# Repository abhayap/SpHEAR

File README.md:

# The *SpHEAR Project

The *SpHEAR (Spherical Harmonics Ear) Project is a collection of 3D models and associated code for building, testing and calibrating full surround Ambisonics microphones. All 3D models are written in Openscad with the code licensed under the GPL 3+ license (GNU Public License version 3 or higher), and the 3D models licensed under the Creative Commons Attribution-NonCommercial-ShareAlike 4.0 International license.

The 3D models are almost completely parametric and are designed to be able to be printed on low cost widely available 3D printers (at CCRMA we use an Ultimaker 2 Extended Plus printer, using PLA material). The design is modular and tries to avoid using overhangs and support structures. That is why each microphone assembly is made of a number of independently printed capsule holders interconnected by legs that interlock and hold the structure together. The capsule holders and the mount are glued together to create a 3D structure that securely holds all microphone capsules. A mount that can be clipped into a standard microphone stand is part of the design.

## Mailing list

You can subscribe to a development mailing list (sphear-devel@ccrma.stanford.edu) here:
<https://cm-mail.stanford.edu/mailman/listinfo/sphear-devel>

## About building microphones

Successfully printing a microphone assembly is only the first step in a long and complicated process. This also includes finding and buying the required microphone capsules, assembling the electronics (requires precision skill with the soldering iron) and finally calibrating the multi-capsule microphone to get the best performance out of it (you will need at least a single driver sound source and a calibrated microphone).

The whole process is not easy and requires knowledge of acoustics and electronics, plus a healthy dose of patience and the ability to perform tasks with precision and care. This repository will eventually include more detailed instructions, electronic schematics, suggested and tested parts and software and procedures for calibrating and measuring the microphone, including models for test and calibration rigs.

## 3D models

The 3D models currently include the TinySpHEAR, a four capsule first order Ambisonics microphone, the Octathingy, an eight capsule second order design by Eric Benjamin and Aaron Heller and preliminary designs for 12 and 20 capsule designs (the BigSpHEAR_12 and BigSpHEAR_20 models). The models will be expanded as testing proceeds. 

* [TinySpHEAR](doc/TinySpHEAR_simple.md): four capsule first order microphone with simple stand mount

  * [TinySpHEAR Zapnspark](doc/TinySpHEAR_zapnspark.md): four capsule first order microphone with four Zapnspark phantom power interfaces and shock mount

* [Octathingy](): eight capsule microphone (proof of concept so far)

* [BigSpHEAR_12 / BigSpHEAR_20](): 12 and 20 capsule designs (proof of concept)

## Electronics

The pcb/zapnspark directory contains the Kicad electrical circuit and printed circuit board design for the Zapnspark phantom power interface. The current printed circuit board design fits into four slots carved inside the body of the [TinySpHEAR plus Zapnspark model](doc/TinySpHEAR_zapnspark.md). Everything is dimensioned for the sizes of the components specified in the parts list, any changes (specially the diameter of the electrolytic capacitors) would need to be taken into account by changing appropriate model parameters. 

## Calibration

The calibration/src directory contains the Octave files for the current calibration software. The CALIBRATION.md file in there has a very brief description of usage, but currently is out of date with the current source code. Look into the individual files for more guidance. Hopefully this will be fixed soon.

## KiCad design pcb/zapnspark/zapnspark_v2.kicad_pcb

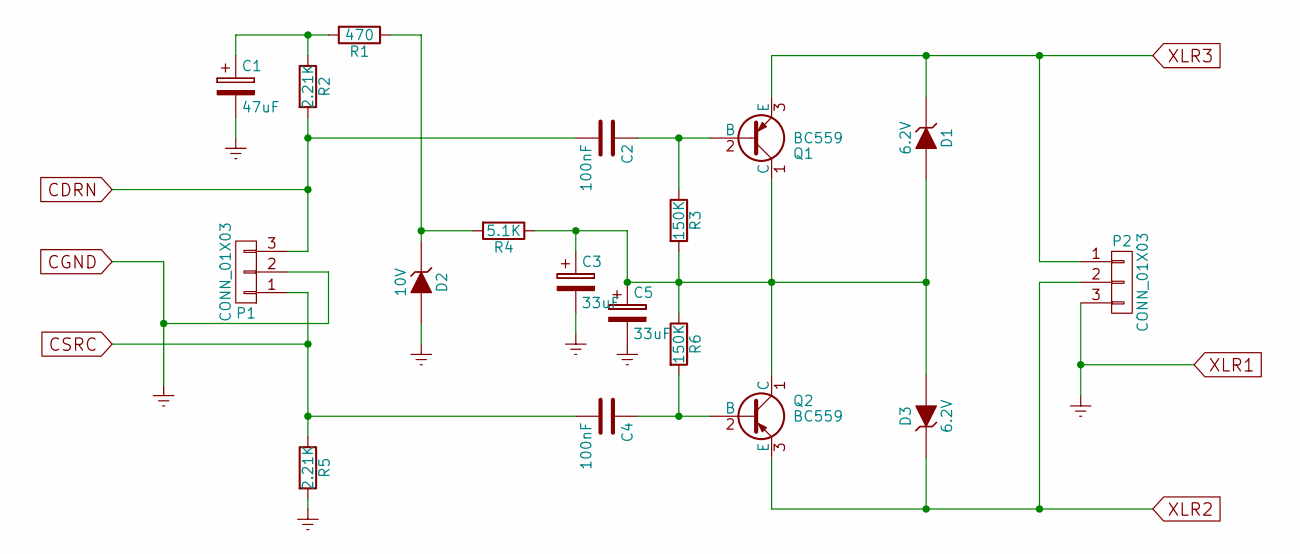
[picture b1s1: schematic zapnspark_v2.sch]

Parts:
C1: 47uF; C_Radial_D8_L13_P3.8
C2, C4: 100nF; C_Rect_L13_W4_P10
C3, C5: 33uF; C_Radial_D8_L13_P3.8
D1, D3: 6.2V; D5
D2: 10V; D5
P1, P2: CONN_01X03; Pin_Header_Angled_1x03
Q1, Q2: BC559; TO-220_Bipolar-BCE_Vertical
R1: 470; Resistor_Horizontal_RM10mm
R2, R5: 2.21K; Resistor_Horizontal_RM10mm
R3, R6: 150K; Resistor_Horizontal_RM10mm
R4: 5.1K; Resistor_Horizontal_RM10mm

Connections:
CDRN: C2.2, P1.3, R2.2
CGND: C1.2, C3.2, C5.2, D2.2 (A), P1.2, P2.3, R5.2
CSRC: C4.2, P1.1, R5.1
unnamed: C1.1, R1.2, R2.1
unnamed: C2.1, Q1.2 (B), R3.1
unnamed: C3.1, C5.1, D1.2 (A), D3.2 (A), Q1.1 (C), Q2.1 (C), R3.2, R4.1, R6.1
unnamed: C4.1, Q2.2 (B), R6.2
unnamed: D2.1 (K), R1.1, R4.2
XLR2: D3.1 (K), P2.2, Q2.3 (E)
XLR3: D1.1 (K), P2.1, Q1.3 (E)

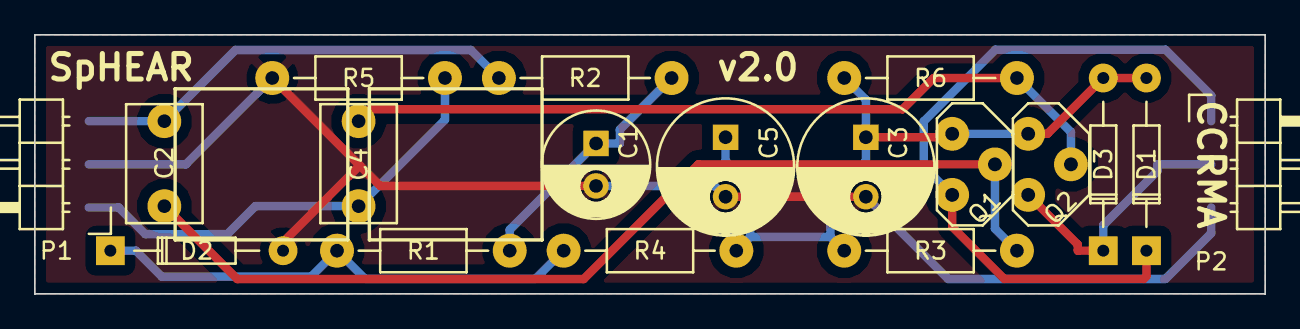
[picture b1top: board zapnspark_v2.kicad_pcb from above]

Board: 2 copper layers, 72.4 x 15.2 mm, 18 parts (0 on the bottom side), 10 nets.
